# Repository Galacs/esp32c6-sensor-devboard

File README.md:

# ESP32-C6 Sensor-Devboard

ESP32-C6 sensor test board made to test step-down power supply design, wide input AC/DC level shifter, i2c temperature sensors, sdio sdcard and RF circuit (IEEE 802.15.4)

## IC List

- ESP32-C6 (Main MCU)
- W25Q128JVSIQ (16MB program storage spi flash)
- TCA9555 (I2C I/O expander)
- 2x TMP117 (I2C temperature sensor)
- BMP581 (I2C/SPI pressure sensor)
- 3x LM393 (comparator)
- 2x LMR36520 (wide Vin buck converter)
- LM317A (high Vin LDO)
- AP2112K (MCU LDO)
- 2x CJ431 (Voltage references)
- 2450AT18A100E (2.45GHz Ceramic chip antenna)

## Top preview

## Preview 3d render

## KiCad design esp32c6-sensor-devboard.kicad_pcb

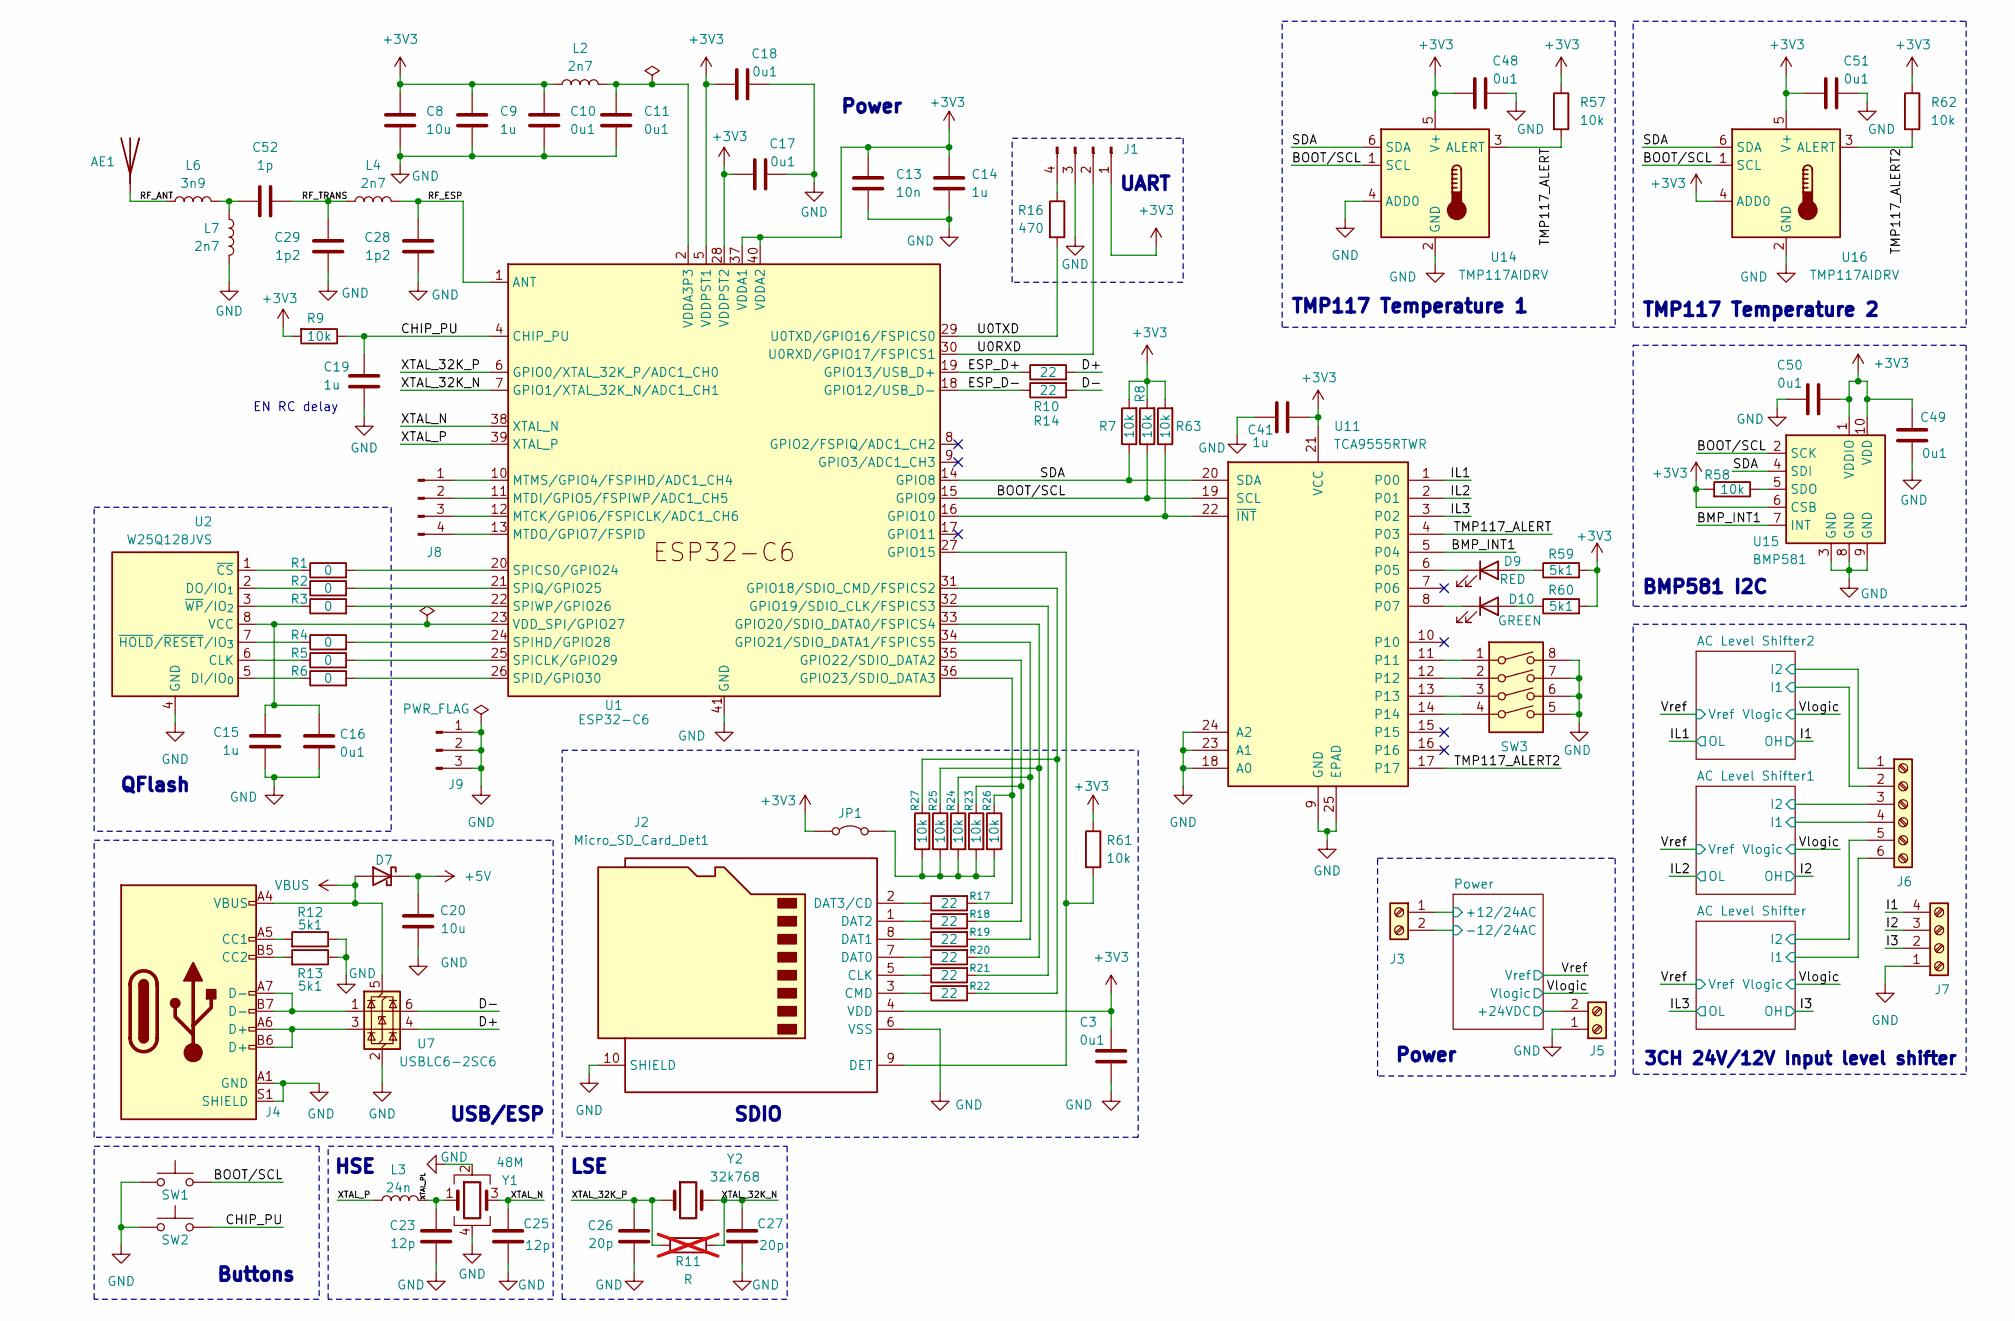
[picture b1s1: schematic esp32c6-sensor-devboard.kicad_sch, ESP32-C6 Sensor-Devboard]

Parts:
AE1: Antenna; Johanson_2450AT18x100; Manufacturer Part Number 2450AT18A100E; JLCPCB Part # C89334
C3: 0u1; C_0603_1608Metric; Manufacturer Part Number CC0603KRX7R9BB104; JLCPCB Part # C14663
C8, C20: 10u; C_0402_1005Metric; Manufacturer Part Number CL05A106MQ5NUNC; JLCPCB Part # C15525
C9, C14, C15, C19, C41: 1u; C_0402_1005Metric; Manufacturer Part Number CL05A105KA5NQNC; JLCPCB Part # C52923
C10, C11, C16, C17, C18, C48, C49, C50, C51: 0u1; C_0402_1005Metric; Manufacturer Part Number CL05B104KB54PNC; JLCPCB Part # C307331
C13: 10n; C_0402_1005Metric; Manufacturer Part Number CL05B103KB5NNNC; JLCPCB Part # C15195
C23, C25: 12p; C_0402_1005Metric; Manufacturer Part Number 0402CG120J500NT; JLCPCB Part # C1547
C26, C27: 20p; C_0402_1005Metric; Manufacturer Part Number 0402CG200J500NT; JLCPCB Part # C1554
C28, C29: 1p2; C_0402_1005Metric; Manufacturer Part Number GJM1555C1H1R2WB01D; JLCPCB Part # C76899
C52: 1p; C_0402_1005Metric; Manufacturer Part Number 0402CG1R0C500NT; JLCPCB Part # C1550
D7: D_Schottky; D_SMA; Manufacturer Part Number SS54; JLCPCB Part # C22452
D9: RED; LED_0603_1608Metric; Manufacturer Part Number KT-0603R; JLCPCB Part # C2286
D10: GREEN; LED_0805_2012Metric; Manufacturer Part Number KT-0805G; JLCPCB Part # C2297
J1, J8: Conn_01x04_Pin; PinHeader_1x04_P2.54mm_Vertical
J2: Micro_SD_Card_Det1; microSD_Hanbo_TF012; Manufacturer Part Number TF-012; JLCPCB Part # C410350
J3, J5: Screw_Terminal_01x02; TerminalBlock_Altech_AK300-2_P5.00mm
J4: USB_C_Receptacle_USB2.0_14P; USB_C_Receptacle_HRO_TYPE-C-31-M-12; Manufacturer Part Number TYPE-C16PIN; JLCPCB Part # C393939
J6: Screw_Terminal_01x06; TerminalBlock_Phoenix_MKDS-1,5-6_1x06_P5.00mm_Horizontal
J7: Screw_Terminal_01x04; TerminalBlock_Altech_AK300-4_P5.00mm
J9: Conn_01x03_Pin; PinHeader_1x03_P2.54mm_Vertical
JP1: Jumper_2_Bridged; PinHeader_1x02_P2.54mm_Vertical
L2, L4: 2n7; L_0402_1005Metric; Manufacturer Part Number LQW15AN2N7G80D; JLCPCB Part # C412269
L3: 24n; L_0402_1005Metric; Manufacturer Part Number LQW15AN24NG00D; JLCPCB Part # C167472
L6: 3n9; L_0402_1005Metric; Manufacturer Part Number LQG15HS3N9S02D; JLCPCB Part # C77109
L7: 2n7; L_0402_1005Metric; Manufacturer Part Number LQG15HS2N7S02D; JLCPCB Part # C77108
R1, R2, R3, R4, R5, R6: 0; R_0402_1005Metric; Manufacturer Part Number 0402WGF0000TCE; JLCPCB Part # C17168
R7, R8, R9, R57, R58, R61, R62, R63: 10k; R_0603_1608Metric; Manufacturer Part Number 0603WAF1002T5E; JLCPCB Part # C25804
R10, R14, R17, R18, R19, R20, R21, R22: 22; R_0402_1005Metric; Manufacturer Part Number 0402WGF220JTCE; JLCPCB Part # C25092
R11: R; R_0603_1608Metric; not fitted
R12, R13, R59, R60: 5k1; R_0603_1608Metric; Manufacturer Part Number 0603WAF5101T5E; JLCPCB Part # C23186
R16: 470; R_0402_1005Metric; Manufacturer Part Number 0402WGF4700TCE; JLCPCB Part # C25117
R23, R24, R25, R26, R27: 10k; R_0402_1005Metric; Manufacturer Part Number 0402WGF1002TCE; JLCPCB Part # C25744
SW1, SW2: SW_Push; SW_SPST_TS-1088-xR020; Manufacturer Part Number TS-1088-AR02016; JLCPCB Part # C720477
SW3: SW_DIP_x04; SW_DIP_SPSTx04_Slide_9.78x12.34mm_W7.62mm_P2.54mm
U1: ESP32-C6; QFN-40-1EP_5x5mm_P0.4mm_EP3.6x3.6mm_ThermalVias; Manufacturer Part Number ESP32-C6; JLCPCB Part # C5364646
U2: W25Q128JVS; SOIC-8_5.3x5.3mm_P1.27mm; Manufacturer Part Number W25Q128JVSIQ; JLCPCB Part # C97521
U7: USBLC6-2SC6; SOT-23-6; Manufacturer Part Number USBLC6-2SC6; JLCPCB Part # C7519
U11: TCA9555RTWR; Texas_RTW_WQFN-24-1EP_4x4mm_P0.5mm_EP2.7x2.7mm_ThermalVias; Manufacturer Part Number TCA9555RTWR; JLCPCB Part # C140277
U14, U16: TMP117AIDRV; WSON-6-1EP_2x2mm_P0.65mm_EP1x1.6mm; Manufacturer Part Number TMP117AIDRVR; JLCPCB Part # C699536
U15: BMP581; Bosch_LGA-10_2x2mm_P0.8mm_AntiClockwisePinNumbering; Manufacturer Part Number BMP581; JLCPCB Part # C5362283
Y1: 48M; Crystal_SMD_2016-4Pin_2.0x1.6mm; Manufacturer Part Number R940000096; JLCPCB Part # C7206306
Y2: 32k768; Crystal_SMD_3215-2Pin_3.2x1.5mm; Manufacturer Part Number Q13FC13500004; JLCPCB Part # C32346

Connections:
+3V3: C3.1, C8.1, C9.1, C10.1, C13.1, C14.1, C17.1, C18.1, C41.2, C48.1, C49.2, C50.1, C51.1, J1.1, J2.4 (VDD), JP1.1 (A), L2.1, R7.2, R8.2, R9.2, R57.1, R58.2, R59.2, R60.2, R61.1, R62.1, R63.2, U1.5 (VDDPST1), U1.28 (VDDPST2), U1.37 (VDDA1), U1.40 (VDDA2), U11.21 (VCC), U14.5 (V+), U15.1 (VDDIO), U15.6 (CSB), U15.10 (VDD), U16.4 (ADD0), U16.5 (V+); also elsewhere on the board
+5V: C20.1, D7.1 (K); also elsewhere on the board
/AC Level Shifter1/I1: J6.4; also elsewhere on the board
/AC Level Shifter1/I2: J6.3; also elsewhere on the board
/AC Level Shifter2/I1: J6.2; also elsewhere on the board
/AC Level Shifter2/I2: J6.1; also elsewhere on the board
/AC Level Shifter/I1: J6.6; also elsewhere on the board
/AC Level Shifter/I2: J6.5; also elsewhere on the board
/BMP_INT1: U11.5 (P04), U15.7 (INT)
/BOOT/SCL: R8.1, SW1.2, U1.15 (GPIO9), U11.19 (SCL), U14.1 (SCL), U15.2 (SCK), U16.1 (SCL)
/CHIP_PU: C19.1, R9.1, SW2.2, U1.4 (CHIP_PU)
/D+: R10.2, U7.4 (I/O2)
/D-: R14.2, U7.6 (I/O1)
/ESP_D+: R10.1, U1.19 (GPIO13/USB_D+)
/ESP_D-: R14.1, U1.18 (GPIO12/USB_D-)
/I1: J7.4; also elsewhere on the board
/I2: J7.3; also elsewhere on the board
/I3: J7.2; also elsewhere on the board
/IL1: U11.1 (P00); also elsewhere on the board
/IL2: U11.2 (P01); also elsewhere on the board
/IL3: U11.3 (P02); also elsewhere on the board
/Power/+12/24AC: J3.1; also elsewhere on the board
/Power/+24VDC: J5.2; also elsewhere on the board
/Power/-12/24AC: J3.2; also elsewhere on the board
/RF_ANT: AE1.1 (A), L6.1
/RF_ESP: C28.1, L4.2, U1.1 (ANT)
/RF_TRANS: C29.1, C52.1, L4.1
/SDA: R7.1, U1.14 (GPIO8), U11.20 (SDA), U14.6 (SDA), U15.4 (SDI), U16.6 (SDA)
/TMP117_ALERT: R57.2, U11.4 (P03), U14.3 (ALERT)
/TMP117_ALERT2: R62.2, U11.17, U16.3 (ALERT)
/U0RXD: J1.2, U1.30 (U0RXD/GPIO17/FSPICS1)
/U0TXD: R16.2, U1.29 (U0TXD/GPIO16/FSPICS0)
/XTAL_32K_N: C27.1, R11.2, U1.7 (GPIO1/XTAL_32K_N/ADC1_CH1), Y2.2
/XTAL_32K_P: C26.2, R11.1, U1.6 (GPIO0/XTAL_32K_P/ADC1_CH0), Y2.1
/XTAL_N: C25.1, U1.38 (XTAL_N), Y1.3
/XTAL_P: L3.1, U1.39 (XTAL_P)
/XTAL_PL: C23.2, L3.2, Y1.1
GND: C3.2, C8.2, C9.2, C10.2, C11.2, C13.2, C14.2, C15.2, C16.2, C17.2, C18.2, C19.2, C20.2, C23.1, C25.2, C26.1, C27.2, C28.2, C29.2, C41.1, C48.2, C49.1, C50.2, C51.2, J1.3, J2.6 (VSS), J2.10 (SHIELD), J4.A1 (GND), J4.A12 (GND), J4.B1 (GND), J4.B12 (GND), J4.S1 (SHIELD), J5.1, J7.1, J9.1, J9.2, J9.3, L7.1, R12.1, R13.1, SW1.1, SW2.1, SW3.5, SW3.6, SW3.7, SW3.8, U1.41 (GND), U2.4 (GND), U7.2 (GND), U11.9 (GND), U11.18 (A0), U11.23 (A1), U11.24 (A2), U11.25 (EPAD), U14.2 (GND), U14.4 (ADD0), U15.3 (GND), U15.8 (GND), U15.9 (GND), U16.2 (GND), U16.7, Y1.2, Y1.4; also elsewhere on the board
unnamed: C11.1, L2.2, U1.2 (VDDA3P3), U1.3 (VDDA3P3)
unnamed: C52.2, L6.2, L7.2
unnamed: D9.2 (A), R59.1
unnamed: D9.1 (K), U11.6 (P05)
unnamed: D10.2 (A), R60.1
unnamed: D10.1 (K), U11.8 (P07)
unnamed: J1.4, R16.1
unnamed: J2.5 (CLK), R21.1
unnamed: J2.3 (CMD), R22.1
unnamed: J2.7 (DAT0), R20.1
unnamed: J2.8 (DAT1), R19.1
unnamed: J2.1 (DAT2), R18.1
unnamed: J2.2 (DAT3/CD), R17.1
unnamed: J2.9 (DET), R61.2, U1.27 (GPIO15)
unnamed: J4.A5 (CC1), R12.2
unnamed: J4.B5 (CC2), R13.2
unnamed: J4.A6 (D+), J4.B6 (D+), U7.3 (I/O2)
unnamed: J4.A7 (D-), J4.B7 (D-), U7.1 (I/O1)
unnamed: J8.1, U1.10 (MTMS/GPIO4/FSPIHD/ADC1_CH4)
unnamed: J8.2, U1.11 (MTDI/GPIO5/FSPIWP/ADC1_CH5)
unnamed: J8.3, U1.12 (MTCK/GPIO6/FSPICLK/ADC1_CH6)
unnamed: J8.4, U1.13 (MTDO/GPIO7/FSPID)
unnamed: JP1.2 (B), R23.2, R24.2, R25.2, R26.2, R27.2
unnamed: R63.1, U1.16 (GPIO10), U11.22 (~INT)
unnamed: R22.2, R27.1, U1.31 (GPIO18/SDIO_CMD/FSPICS2)
unnamed: R21.2, U1.32 (GPIO19/SDIO_CLK/FSPICS3)
unnamed: R20.2, R25.1, U1.33 (GPIO20/SDIO_DATA0/FSPICS4)
unnamed: R19.2, R24.1, U1.34 (GPIO21/SDIO_DATA1/FSPICS5)
unnamed: R18.2, R23.1, U1.35 (GPIO22/SDIO_DATA2)
unnamed: R17.2, R26.1, U1.36 (GPIO23/SDIO_DATA3)
unnamed: R5.2, U1.25 (SPICLK/GPIO29)
unnamed: R1.2, U1.20 (SPICS0/GPIO24)
unnamed: R6.2, U1.26 (SPID/GPIO30)
unnamed: R4.2, U1.24 (SPIHD/GPIO28)
unnamed: R2.2, U1.21 (SPIQ/GPIO25)
unnamed: R3.2, U1.22 (SPIWP/GPIO26)
unnamed: C15.1, C16.1, U1.23 (VDD_SPI/GPIO27), U2.8 (VCC)
unnamed: R5.1, U2.6 (CLK)
unnamed: R6.1, U2.5 (DI/IO_{0})
unnamed: R2.1, U2.2 (DO/IO_{1})
unnamed: R1.1, U2.1 (~CS)
unnamed: R4.1, U2.7 (~HOLD/~RESET/IO_{3})
unnamed: R3.1, U2.3 (~WP/IO_{2})
unnamed: SW3.1, U11.11
unnamed: SW3.2, U11.12
unnamed: SW3.3, U11.13
unnamed: SW3.4, U11.14
unnamed: R58.1, U15.5 (SDO)
TMP117_1_PAD: U14.7
VBUS: D7.2 (A), J4.A4 (VBUS), J4.A9 (VBUS), J4.B4 (VBUS), J4.B9 (VBUS), U7.5 (VBUS)

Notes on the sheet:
BMP581 I2C
TMP117 Temperature 2
EN RC delay
HSE
3CH 24V/12V Input level shifter
SDIO
LSE
TMP117 Temperature 1
QFlash
Power
USB/ESP
Buttons
UART

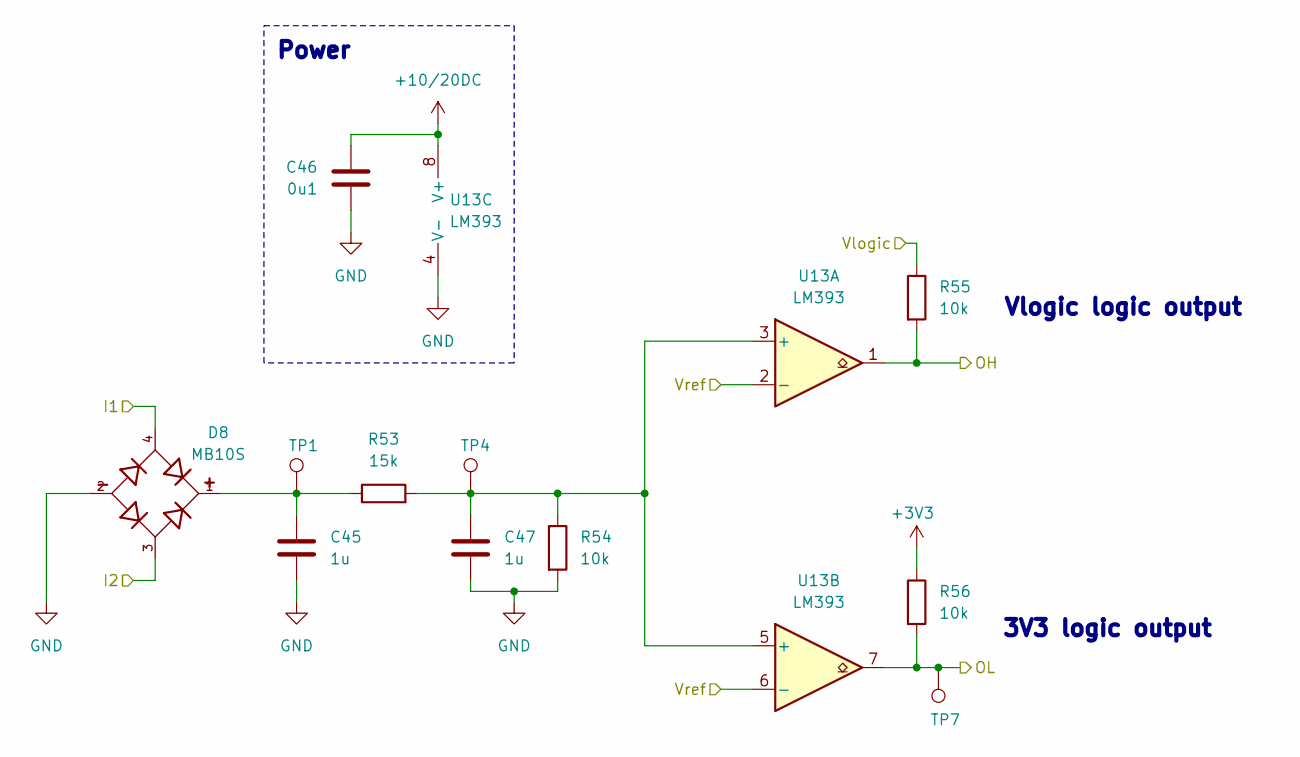
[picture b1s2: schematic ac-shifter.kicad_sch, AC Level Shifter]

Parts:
C45: 1u; C_0603_1608Metric; Manufacturer Part Number CL10A105KB8NNNC; JLCPCB Part # C15849
C46: 0u1; C_0402_1005Metric; Manufacturer Part Number CL05B104KB54PNC; JLCPCB Part # C307331
C47: 1u; C_0402_1005Metric; Manufacturer Part Number CL05A105KA5NQNC; JLCPCB Part # C52923
D8: MB10S; OnSemi_751EP_SOIC-4_3.9x4.725mm_P2.54mm; Manufacturer Part Number C2488; JLCPCB Part # C2488
R53: 15k; R_0603_1608Metric; Manufacturer Part Number 0603WAF1502T5E; JLCPCB Part # C22809
R54, R55, R56: 10k; R_0603_1608Metric; Manufacturer Part Number 0603WAF1002T5E; JLCPCB Part # C25804
TP1, TP4, TP7: TestPoint; TestPoint_Pad_D2.0mm
U13: LM393; SOIC-8_3.9x4.9mm_P1.27mm; Manufacturer Part Number LM393DR2G; JLCPCB Part # C7955

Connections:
+3V3: R56.1; also elsewhere on the board
+10/20DC: C46.1, U13.8 (V+); also elsewhere on the board
/AC Level Shifter/I1: D8.4; also elsewhere on the board
/AC Level Shifter/I2: D8.3; also elsewhere on the board
/I3: R55.2, U13.1; also elsewhere on the board
/IL3: R56.2, TP7.1, U13.7; also elsewhere on the board
/Vlogic: R55.1; also elsewhere on the board
/Vref: U13.2 (-), U13.6 (-); also elsewhere on the board
GND: C45.2, C46.2, C47.2, D8.2, R54.2, U13.4 (V-); also elsewhere on the board
unnamed: C45.1, D8.1, R53.1, TP1.1
unnamed: C47.1, R53.2, R54.1, TP4.1, U13.3 (+), U13.5 (+)

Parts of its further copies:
C32, C42: 1u; C_0603_1608Metric; Manufacturer Part Number CL10A105KB8NNNC; JLCPCB Part # C15849
C39, C43: 0u1; C_0402_1005Metric; Manufacturer Part Number CL05B104KB54PNC; JLCPCB Part # C307331
C40, C44: 1u; C_0402_1005Metric; Manufacturer Part Number CL05A105KA5NQNC; JLCPCB Part # C52923
D5, D6: MB10S; OnSemi_751EP_SOIC-4_3.9x4.725mm_P2.54mm; Manufacturer Part Number C2488; JLCPCB Part # C2488
R37, R49: 15k; R_0603_1608Metric; Manufacturer Part Number 0603WAF1502T5E; JLCPCB Part # C22809
R39, R47, R48, R50, R51, R52: 10k; R_0603_1608Metric; Manufacturer Part Number 0603WAF1002T5E; JLCPCB Part # C25804
TP2, TP3, TP5, TP6, TP8, TP9: TestPoint; TestPoint_Pad_D2.0mm
U10, U12: LM393; SOIC-8_3.9x4.9mm_P1.27mm; Manufacturer Part Number LM393DR2G; JLCPCB Part # C7955

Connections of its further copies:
+3V3: R48.1, R52.1; also elsewhere on the board
+10/20DC: C39.1, C43.1, U10.8 (V+), U12.8 (V+); also elsewhere on the board
/AC Level Shifter1/I1: D6.4; also elsewhere on the board
/AC Level Shifter1/I2: D6.3; also elsewhere on the board
/AC Level Shifter2/I1: D5.4; also elsewhere on the board
/AC Level Shifter2/I2: D5.3; also elsewhere on the board
/I1: R47.2, U10.1; also elsewhere on the board
/I2: R51.2, U12.1; also elsewhere on the board
/IL1: R48.2, TP9.1, U10.7; also elsewhere on the board
/IL2: R52.2, TP8.1, U12.7; also elsewhere on the board
/Vlogic: R47.1, R51.1; also elsewhere on the board
/Vref: U10.2 (-), U10.6 (-), U12.2 (-), U12.6 (-); also elsewhere on the board
GND: C32.2, C39.2, C40.2, C42.2, C43.2, C44.2, D5.2, D6.2, R39.2, R50.2, U10.4 (V-), U12.4 (V-); also elsewhere on the board
unnamed: C32.1, D5.1, R37.1, TP3.1
unnamed: C42.1, D6.1, R49.1, TP2.1
unnamed: C40.1, R37.2, R39.1, TP6.1, U10.3 (+), U10.5 (+)
unnamed: C44.1, R49.2, R50.1, TP5.1, U12.3 (+), U12.5 (+)

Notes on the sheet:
Power
3V3 logic output
Vlogic logic output

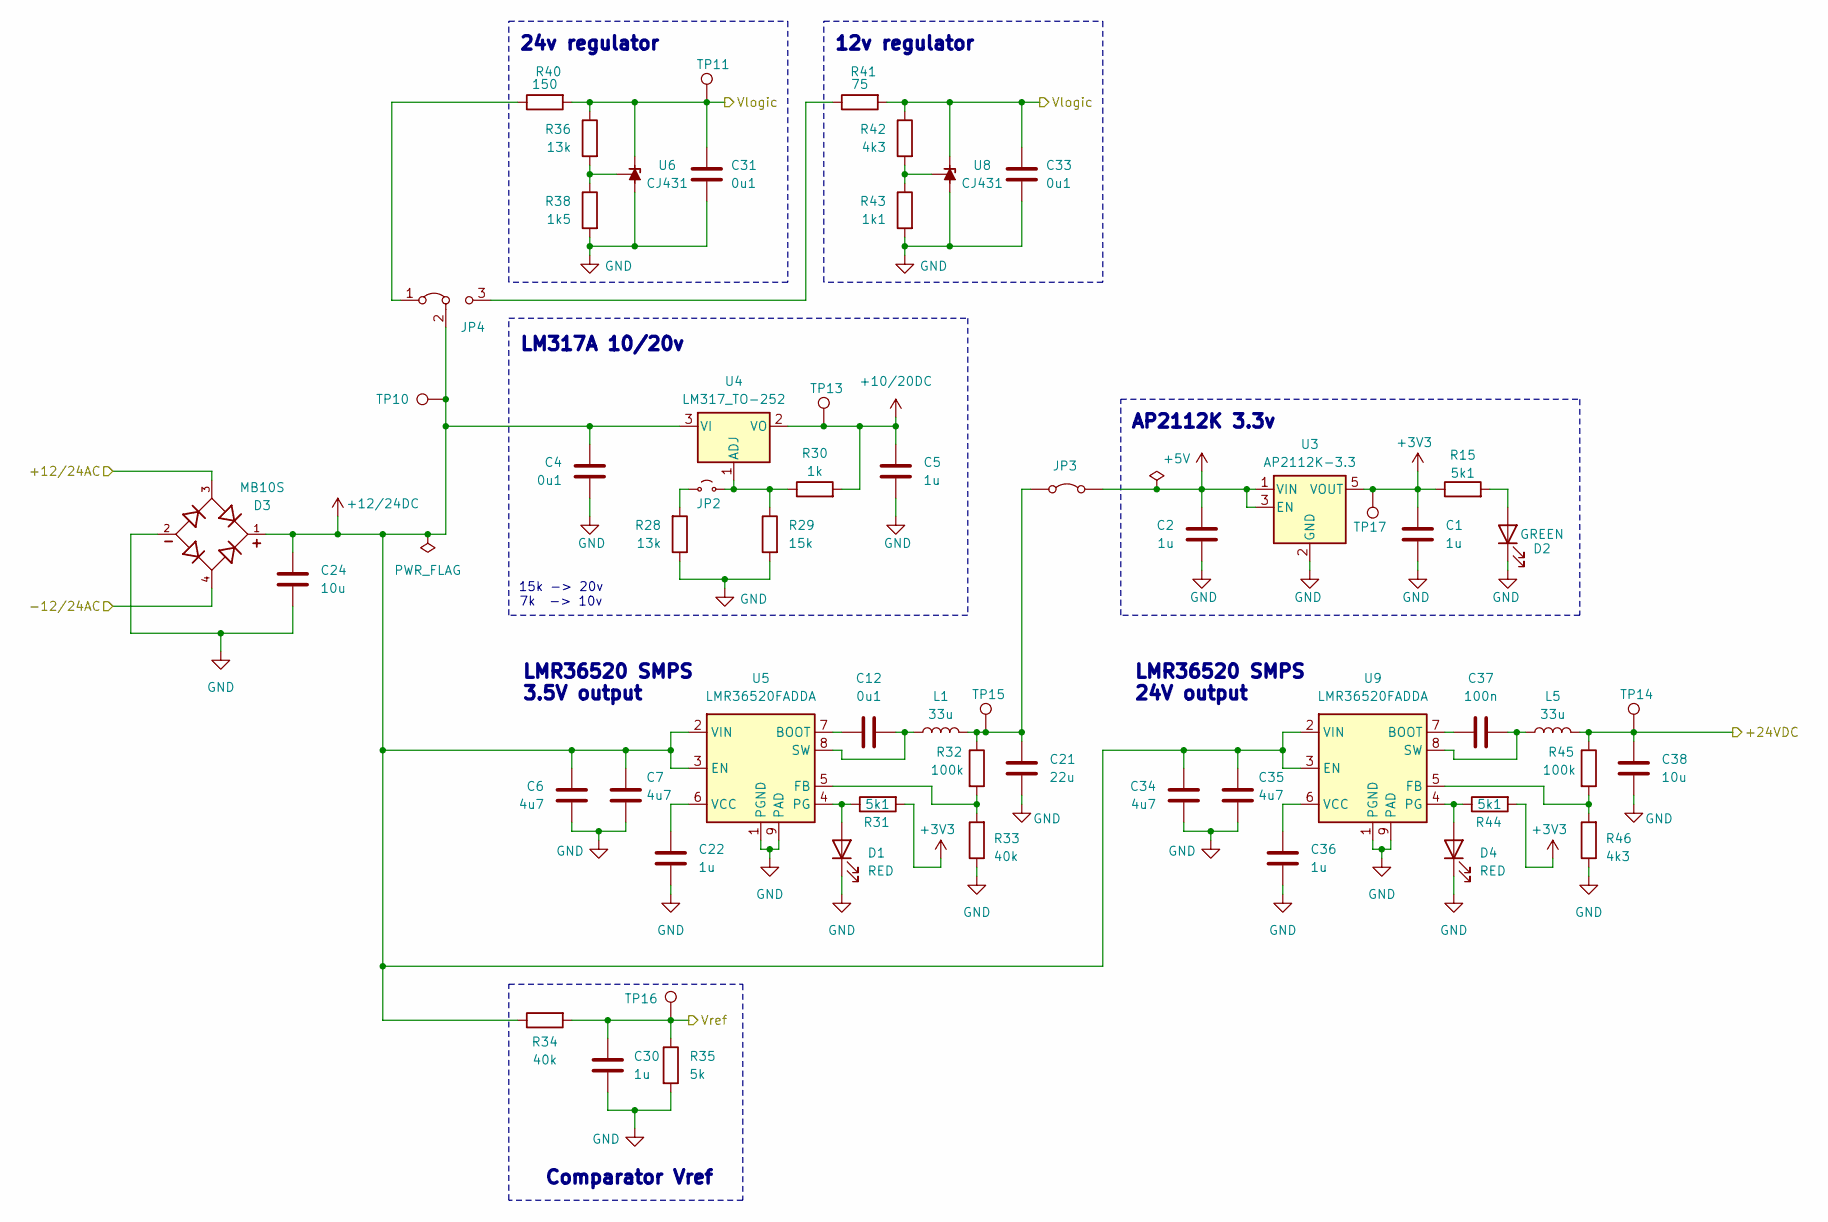
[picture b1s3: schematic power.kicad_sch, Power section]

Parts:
C1, C2, C5: 1u; C_0603_1608Metric; Manufacturer Part Number CL10A105KB8NNNC; JLCPCB Part # C15849
C4: 0u1; C_0603_1608Metric; Manufacturer Part Number CC0603KRX7R9BB104; JLCPCB Part # C14663
C6, C7, C34, C35: 4u7; C_1206_3216Metric; Manufacturer Part Number 1206B475K500NT; JLCPCB Part # C29823
C12, C31, C33: 0u1; C_0402_1005Metric; Manufacturer Part Number CL05B104KB54PNC; JLCPCB Part # C307331
C21: 22u; C_0603_1608Metric; Manufacturer Part Number CL10A226MQ8NRNC; JLCPCB Part # C59461
C22, C30, C36: 1u; C_0402_1005Metric; Manufacturer Part Number CL05A105KA5NQNC; JLCPCB Part # C52923
C24: 10u; C_0805_2012Metric; Manufacturer Part Number GRM21BR61H106KE43L; JLCPCB Part # C440198
C37: 100n; C_0402_1005Metric; Manufacturer Part Number CL05B104KB54PNC; JLCPCB Part # C307331
C38: 10u; C_0603_1608Metric; Manufacturer Part Number CL10A106MA8NRNC; JLCPCB Part # C96446
D1, D4: RED; LED_0603_1608Metric; Manufacturer Part Number KT-0603R; JLCPCB Part # C2286
D2: GREEN; LED_0805_2012Metric; Manufacturer Part Number KT-0805G; JLCPCB Part # C2297
D3: MB10S; OnSemi_751EP_SOIC-4_3.9x4.725mm_P2.54mm; Manufacturer Part Number C2488; JLCPCB Part # C2488
JP2: Jumper_2_Small_Open; PinHeader_1x02_P2.54mm_Vertical
JP3: Jumper_2_Bridged; PinHeader_1x02_P2.54mm_Vertical
JP4: Jumper_3_Bridged12; PinHeader_1x03_P2.54mm_Vertical
L1, L5: 33u; L_Chilisin_BMRx00060630; Manufacturer Part Number FXL0630-330-M; JLCPCB Part # C177245
R15, R31, R44: 5k1; R_0603_1608Metric; Manufacturer Part Number 0603WAF5101T5E; JLCPCB Part # C23186
R28, R36: 13k; R_0603_1608Metric; Manufacturer Part Number 0603WAF1302T5E; JLCPCB Part # C22797
R29: 15k; R_0603_1608Metric; Manufacturer Part Number 0603WAF1502T5E; JLCPCB Part # C22809
R30: 1k; R_0603_1608Metric; Manufacturer Part Number 0603WAF1001T5E; JLCPCB Part # C21190
R32, R45: 100k; R_0603_1608Metric; Manufacturer Part Number 0603WAF1003T5E; JLCPCB Part # C25803
R33, R34: 40k; R_0603_1608Metric; Manufacturer Part Number 0603WAF4022T5E; JLCPCB Part # C12447
R35: 5k; R_0603_1608Metric; Manufacturer Part Number 0603WAF4991T5E; JLCPCB Part # C23046
R38: 1k5; R_0603_1608Metric; Manufacturer Part Number 0603WAF1501T5E; JLCPCB Part # C22843
R40: 150; R_0805_2012Metric; Manufacturer Part Number 0805W8F1500T5E; JLCPCB Part # C17471
R41: 75; R_0805_2012Metric; Manufacturer Part Number 0805W8F750JT5E; JLCPCB Part # C20638
R42, R46: 4k3; R_0603_1608Metric; Manufacturer Part Number 0603WAF4301T5E; JLCPCB Part # C23159
R43: 1k1; R_0603_1608Metric; Manufacturer Part Number 0603WAF1101T5E; JLCPCB Part # C22764
TP10, TP11, TP13, TP14, TP15, TP16, TP17: TestPoint; TestPoint_Pad_D2.0mm
U3: AP2112K-3.3; SOT-23-5; Manufacturer Part Number AP2112K-3.3TRG1; JLCPCB Part # C51118
U4: LM317_TO-252; TO-252-2; Manufacturer Part Number LM317AG-TN3-R; JLCPCB Part # C75510
U5, U9: LMR36520FADDA; Texas_HTSOP-8-1EP_3.9x4.9mm_P1.27mm_EP2.95x4.9mm_Mask2.4x3.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; Manufacturer Part Number LMR36520FADDAR; JLCPCB Part # C1858395
U6, U8: CJ431; SOT-23; Manufacturer Part Number CJ431; JLCPCB Part # C3113

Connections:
+3V3: C1.1, R15.1, R31.2, R44.2, TP17.1, U3.5 (VOUT); also elsewhere on the board
+5V: C2.1, JP3.2 (B), U3.1 (VIN), U3.3 (EN); also elsewhere on the board
+10/20DC: C5.1, R30.2, TP13.1, U4.2 (VO); also elsewhere on the board
+12/24DC: C4.1, C6.1, C7.1, C24.1, C34.1, C35.1, D3.1, JP4.2 (C), R34.1, TP10.1, U4.3 (VI), U5.2 (VIN), U5.3 (EN), U9.2 (VIN), U9.3 (EN)
/Power/+12/24AC: D3.3; also elsewhere on the board
/Power/+24VDC: C38.2, L5.2, R45.1, TP14.1; also elsewhere on the board
/Power/-12/24AC: D3.4; also elsewhere on the board
/Vlogic: C31.1, C33.1, R36.1, R40.2, R41.2, R42.1, TP11.1, U6.2 (K), U8.2 (K); also elsewhere on the board
/Vref: C30.1, R34.2, R35.1, TP16.1; also elsewhere on the board
GND: C1.2, C2.2, C4.2, C5.2, C6.2, C7.2, C21.1, C22.2, C24.2, C30.2, C31.2, C33.2, C34.2, C35.2, C36.2, C38.1, D1.1 (K), D2.1 (K), D3.2, D4.1 (K), R28.1, R29.2, R33.1, R35.2, R38.2, R43.2, R46.1, U3.2 (GND), U5.1 (PGND), U5.9 (PAD), U6.3 (A), U8.3 (A), U9.1 (PGND), U9.9 (PAD); also elsewhere on the board
unnamed: D1.2 (A), R31.1, U5.4 (PG)
unnamed: D2.2 (A), R15.2
unnamed: D4.2 (A), R44.1, U9.4 (PG)
unnamed: JP2.1 (A), R28.2
unnamed: JP2.2 (B), R29.1, R30.1, U4.1 (ADJ)
unnamed: C21.2, JP3.1 (A), L1.2, R32.1, TP15.1
unnamed: JP4.1 (A), R40.1
unnamed: JP4.3 (B), R41.1
unnamed: C12.2, U5.7 (BOOT)
unnamed: R32.2, R33.2, U5.5 (FB)
unnamed: C12.1, L1.1, U5.8 (SW)
unnamed: C22.1, U5.6 (VCC)
unnamed: R36.2, R38.1, U6.1 (REF)
unnamed: R42.2, R43.1, U8.1 (REF)
unnamed: C37.2, U9.7 (BOOT)
unnamed: R45.2, R46.2, U9.5 (FB)
unnamed: C37.1, L5.1, U9.8 (SW)
unnamed: C36.1, U9.6 (VCC)

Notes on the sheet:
Comparator Vref
LMR36520 SMPS 3.5V output
AP2112K 3.3v
12v regulator
15k -> 20v 7k -> 10v
24v regulator
LMR36520 SMPS 24V output
LM317A 10/20v

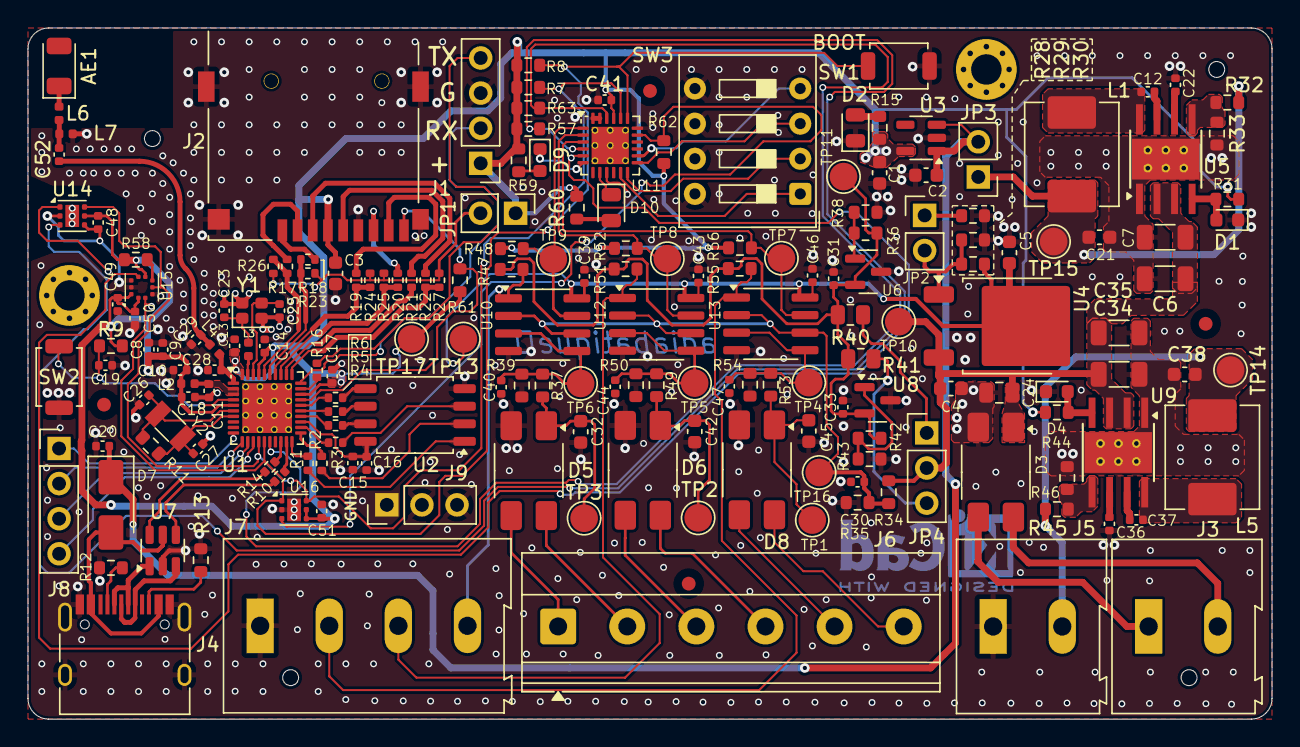
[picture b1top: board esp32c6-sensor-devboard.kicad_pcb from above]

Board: 4 copper layers, 90.0 x 50.0 mm, 183 parts (0 on the bottom side), 115 nets.

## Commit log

2025-09-07 schem: add esp32-c6 symbol
2025-09-07 schem: add W25Q128JVS 16MB flash
2025-09-07 schem: add low and high speed crystals
2025-09-07 schem: add strapping pins and btns
2025-09-07 schem: add usb c connector
2025-09-07 schem: add AP2112K 3.3v ldo regulator
2025-09-07 schem: add rf antenna
2025-09-07 schem: clean up
2025-09-08 schem: add uart header
2025-09-08 schem: add uart series restistor
2025-09-08 schem: add sdcard slot
2025-09-09 schem: reorganize
2025-09-11 schem: update positions
2025-09-15 schem: add LM317A 10/20v ldo
2025-09-15 schem: add sdio nets area rule
2025-09-17 schem: add LMR36520 components
2025-09-17 schem: add LMR36520 components values
2025-09-19 schem: add SMPS power input
2025-09-19 schem: move power to subsheet and add rectifier
2025-09-21 schem: add ac 24/12v level shifter
2025-09-22 schem: add CJ431 24v & 12v voltage references
2025-09-23 schem: add LMR36520 24v smps
2025-09-23 schem: annotate back ac level shifter page
2025-09-24 schem: add TCA9555 I/O expander
2025-09-24 schem: add 3CH 24V/12V Input level shifter
2025-09-24 schem: add comparator test points
2025-09-24 schem: add power test points
2025-09-26 schem: add TMP117 temperature sensor
2025-09-26 schem: add BMP581 I2C pressure sensor
2025-09-26 schem: BMP581 I2C CSB selection
2025-09-26 schem: add 2 LED indicators
2025-09-26 schem: add dip switches
2025-09-26 schem: add spare pins headers
2025-09-26 schem: annotation clean up
2025-09-26 schem: add SD card DET pull-up
2025-09-26 schem: add no connects
2025-09-26 schem: add sheet titles
2025-09-26 schem: fix erc
2025-09-27 schem: fix alignement
2025-09-27 schem: add second TMP117 temp sensor
2025-09-27 schem: connect TCA9555 IO expander INT pin
2025-09-27 schem: add +3V3 test point
2025-09-27 schem: assign netclasses
2025-09-27 schem: assign footprints
2025-09-27 schem: add part numbers to BOM
2025-09-28 schem: add PCA9555 interupt pin pull-up
2025-09-28 schem: add remaining part numbers to BOM
2025-09-28 schem: fix UBS C receptacle hidden power pins
2025-09-28 schem: add missing net classes
2025-09-28 pcb: create pcb file
2025-09-28 pcb: import stackup
2025-09-28 pcb: import components from schematic
2025-09-28 schem/pcb: update MB10S footprint
2025-09-28 pcb: add missing 3d models
2025-09-28 pcb: set net classes colors
2025-09-28 pcb: initial rough pcb placement
2025-09-28 schem/pcb: add antenna matching network
2025-09-29 pcb: smps layout
2025-09-29 pcb: ldos layout
2025-09-29 pcb: shunt regulators layout
2025-09-29 pcb: usb connector layout
2025-09-29 pcb: ac level shifter layout
2025-09-29 pcb: rf layout
2025-09-29 pcb: spi flash layout
2025-09-29 pcb: fix 3v3 ldo layout
2025-09-29 pcb: refine layout
2025-09-29 pcb: area reduction
2025-09-29 pcb: add board outline
2025-09-29 pcb: add inner gnd planes
2025-09-29 pcb: add tooling holes
2025-09-29 pcb: add M2 mounting holes
2025-09-29 pcb: add fiducials
2025-09-29 pcb: add gnd vias
2025-09-29 pcb: add smps routing
2025-09-30 pcb: add rf routing
2025-10-01 pcb: add HSE routing
2025-10-01 pcb: add LSE routing
2025-10-01 pcb: add spi flash routing
2025-10-01 pcb: clean up spi flash routing
2025-10-01 pcb: add usb routing
2025-10-01 pcb: add sdio routing
2025-10-01 pcb: add uart routing
2025-10-01 pcb: add I2C routing
2025-10-01 pcb: add BMP581 routing
2025-10-01 pcb: fix bottom layer traces
2025-10-02 pcb: increase footprints via sizes
2025-10-02 pcb: add TMP1117 temps routing
2025-10-02 pcb: add TCA9555 routing
2025-10-02 pcb: add level shifter routing
2025-10-02 pcb: power rectifier routing
2025-10-02 pcb: add 10/20v ldo routing
2025-10-02 pcb: 24/12v shunt regulators routing
2025-10-02 pcb: comparator routing
2025-10-02 pcb: spare gpio routing
2025-10-02 pcb: add 3v3 ldo routing
2025-10-02 pcb: add first 3v3 power routing
2025-10-02 pcb: add 3v3 routing
2025-10-02 pcb: add CHIP_PU routing
2025-10-02 pcb: add LM393 vcc routing
2025-10-02 pcb: add Vlogic routing
2025-10-02 pcb: add 5v routing
2025-10-02 pcb: add smps leds routing
2025-10-02 pcb: add interupts routing
2025-10-02 pcb: increase TMP117 1 keepout size
2025-10-02 pcb: clean trace appearance
2025-10-02 pcb: add Vref routing
2025-10-02 pcb: add top gnd pour
2025-10-02 pcb: add bottom 3v3 pour
2025-10-02 pcb: remove unused pads
2025-10-02 pcb: make TMP117 keepout area go trough all layers
2025-10-02 pcb: fix TMP117 bottom heatsink copper
2025-10-04 pcb: add stitching vias
2025-10-05 pcb: add more stitching vias
2025-10-05 pcb: left side ref designators silkscreen layout
2025-10-06 pcb: finish silkscreen reference placement
2025-10-06 pcb: remove vias from usb traces
2025-10-06 pcb: add title
2025-10-06 pcb: add bottom silkscreen
2025-10-06 pcb: run and fix DRC
2025-10-06 pcb: add production files
2025-10-08 add README.md
2025-10-12 add render images to README
2025-11-30 fix README title
